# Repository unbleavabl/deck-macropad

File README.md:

# Handwired macropad (tilted deck)

12 MX keys, 2 EC11 encoders, 3 slide pots and 5 small OLED screens on a 30 degree wedge with a phone slot across the back. Handwired; an optional plate PCB that replaces the plate wiring is in `pcb/`. Runs on an STM32F411 "BlackPill" with QMK, USB-C only, no battery.

Everything lives in [`macropad/`](macropad/); file paths below are relative to it.

```
 +---------------------------------------------+
 | ========== phone slot (recessed) ========== |   back, 100 mm tall
 |                                             |
 |  ||   ||   ||   [K1]  [K2]  [K3]           |
 |  ||   ||   ||   [K4]  [K5]  [K6]    (E2)   |
 |  ||   ||   ||   [K7]  [K8]  [K9]    [S5]   |
 |  ||   ||   ||   [K10] [K11] [K12]   (E1)   |
 | [S1] [S2] [S3]                      [S4]   |   front, 13 mm tall
 +---------------------------------------------+
                  177 x 150 mm
```

Keys on a 21 mm grid (about 3 mm between caps), centred between the slider screens and the knob column, 5 mm margins each side; E2 is level with the top key row and E1 sits just behind S4. Each screen sits in front of its slider or knob. Every outside edge is rounded (2.5 mm, vertical corners 6 mm).

```
```

Beginner step-by-step guide with illustrations: `build-guide.pdf` (exported from the live doc at https://claude.ai/code/artifact/070e5841-1c04-4409-ae30-39a42349cde0; re-export after editing it).

Plate PCB (optional, replaces step 4 of the assembly and the plate end of the wiring; lid unchanged): `pcb/README.md`.

Full wiring diagram: `wiring/wiring.html` (regenerate with `wiring/build.py`), published at https://claude.ai/artifact/4pcYRyfMjdKxRtB2dDA4gZ. One drawing, to scale, shows the case opened up for wiring: lid (BlackPill, multiplexer, buttons) on top, turned round, plate underside below, their back edges at the fold. Bare copper buses are thick lines, insulated wires thin. The 27 wires between plate and lid are soldered at the plate end, gather along its back edge into five flat ribbons, and end in five multi-pin Dupont plugs on header pins, so the lid unplugs; each wire's number is on its line and in the harness table. Click a part, bus or number to see only its wires.

Firmware: QMK for the BlackPill in `firmware/deck` (keymaps `default` and `test`, layout and daemon below). The pin map below is final. Screens: Quantum Painter's `sh1106_i2c` driver (it covers the SSD1306), 128x64 at 0x3C, on I2C1 (B6 / B7, 400 kHz); before drawing to a screen, write `1 << channel` to the TCA9548A at 0x70.

## Parts

| Part | Qty | Notes |
|---|---|---|
| STM32F411CEU6 "BlackPill" (WeAct or clone) | 1 | chip must read STM32F411CEU6, crystal 25.000 |
| MX switches | 12 | |
| EC11 encoder, 5 pin (with push) | 2 | have |
| Bourns PTA4543-2015DPB103 slide pot (45 mm, 10k linear) | 3 | caps printed: `case/stl/knobs-caps/fader_cap.stl` |
| 0.96" OLED 128x64 SSD1306, 4-pin I2C | 5 | have; SDA SCL GND VCC from the back, all at address 0x3C |
| TCA9548A I2C multiplexer breakout | 1 | one channel per screen, since they all share one address; hot-glued in the lid |
| 1N4148 diode, through-hole | 14 | 12 keys + 2 encoder pushes |
| 100 nF ceramic capacitor | 3 | one per slider, beside its body: pin 2 to the GND back bus |
| 6x6 mm tactile switch, 5 mm tall | 2 | have; B (BOOT0) and R (reset) in the lid |
| Solid-core wire 24-26 AWG | 2 colours | rows / columns |
| Silicone wire 28-30 AWG | several colours | jumpers on the plate; use the wiring page's colours |
| Rainbow ribbon cable, 1.27 mm pitch | ~1 m | the 27 plate-to-lid wires, as five ribbons |
| Male header strip, 2.54 mm | 2 x 20 + mux | soldered on the BlackPill and multiplexer, long pins up |
| Dupont housings + female crimps | 1x10 x2, 1x5, 1x3, 1x1 | plugs A-E (below); or F-F jumpers cut and soldered |
| M3 x 8 flat-head (countersunk) screw | 10 | 4 plate (2 into the frame, 2 into the dock), 2 dock strip, 4 lid; they cut their own thread in the printed holes, no inserts. M3 x 10 grips better |
| Hot glue | | slide pots and screens sit on printed pegs under the plate; BlackPill and buttons in the lid |
| Rubber feet | 4 | |
| Keycaps 1u | 12 | printed: `case/stl/keycaps/` (flat, black, pressed-in labels) |
| ST-Link V2 (optional) | 1 | rescue flashing over SWD if USB DFU fails |

## Matrix and pins

4 rows x 4 columns, `col2row`: diode anode on the switch, **black band toward the row wire**. Column 3 holds only the two encoder pushes, each on the row nearest it; the push pin nearer the keys takes the diode.

```
          col0 (A7)   col1 (A8)   col2 (A15)  col3 (B0)
row0 A4     K1          K2          K3          E2 push
row1 A5     K4          K5          K6          -
row2 A6     K7          K8          K9          E1 push
row3 B14    K10         K11         K12         -
```

| Signal | BlackPill pin |
|---|---|
| Encoder 1 A / B | B1 / B8 |
| Encoder 2 A / B | B9 / A0 |
| Encoder C (middle of the 3 pins, both) | G |
| Slide pot pin 2 (wiper), sliders 1 / 2 / 3 | A1 / A2 / A3 (ADC1_IN1-3) |
| Slide pot pin 1 (all three) | 3V3 |
| Slide pot pin 3 (all three, alone at the front end) | G, by a short jumper to its own screen's GND pin; 100 nF beside the slider (right of it, from the back), pin 2 to the GND back bus |
| Screens GND / VCC (all five) | G / 3V3 |
| Multiplexer SCL / SDA (I2C1) | B6 / B7 |
| Multiplexer VIN / GND | 3V3 / G |
| Screen SDA / SCL, S1 S2 S3 S4 (E1) S5 (E2) | mux channels 0 1 2 3 4 (SDn / SCn) |
| R button | R (NRST) and G |
| B button | across the board's own BOOT0 button (BOOT0 has no pin hole) |

Avoid: A9 (USB VBUS sense, internal pull-down), A10 (can stop DFU), A11 / A12 (USB), B2 (BOOT1), C13 (LED), C14 / C15 (32 kHz crystal). B14 is row 3. Free: B3, B4, B5, B10, B12, B13, B15. A0 shares the board's KEY button, which is fine for an encoder input. A4-A7 also go to the optional SPI flash footprint on the back: fine as long as no flash chip is fitted. Pin caveats from the [QMK BlackPill notes](https://docs.qmk.fm/platformdev_blackpill_f4x1).

**Plugs on the header pins** (mark pin 1 of each plug and its header):

| Plug | Pins | Wires |
|---|---|---|
| A, 1x10 | BlackPill A0 A1 A2 A3 A4 A5 A6 A7 B0 B1 | 14 15 16 17 1 2 3 5 8 11 |
| B, 1x10 | mux SD0 SC0 SD1 SC1 ... SD4 SC4 | 18-27 |
| C, 1x5 | B8 B9 (5V empty) G 3V3 | 12 13 9 10 |
| D, 1x3 | B14 (B15 empty) A8 | 4 6 |
| E, 1x1 | A15 | 7 |

The lid's own wires: mux SCL / SDA to B6 / B7, mux GND / VIN to G / 3V3 on the other header, and the two buttons.

**Wiring happens upside down, so everything is mirrored.** From below, K1 is at the top right, the sliders are on the right and the knob column is at the left.

## Flashing

- USB DFU: hold B, tap R, let go of B; the board shows up as `STM Device in DFU Mode` (`lsusb`). Flash with `dfu-util` / `qmk flash`. If it won't enter DFU, retry, or add a 22k pull-up on A10.
- A `QK_BOOT` key in the keymap covers day-to-day flashing.
- Rescue: ST-Link V2 on the 4-pin SWD header (3V3 sense, DIO = PA13, SCK = PA14, G), board powered over USB. `st-info --probe` should report chip id `0x431`; `st-flash write firmware.bin 0x08000000`.

## Case (case/)

Rebuild every STL and preview with `case/build.sh` (OpenSCAD 2021.01).

```
case/
  build.sh        all STLs + previews
  diagram.py      preview/assembly.png (run by build.sh)
  scad/
    common.scad   shared sizes: key grid, switch/encoder holes, screws, screen module, lid
    deck.scad     the deck: plate, phone dock, frame, lid
    parts.scad    encoder knobs and spacers, slider caps, fit tests
    keycaps.scad  flat keycaps and their pressed-in labels
    fonts/        DeckIcons.ttf: Material Symbols Rounded, filled, weight 600, for the label icons
    exploded.scad exploded view for the diagram (not a print)
  stl/
    fit-tests/    print these first
    deck/         plate, frame, lid
    knobs-caps/   knobs, encoder spacers, slider caps
    keycaps/      keycap, label set (body + legend), blank label
  3mf/            ready-to-print Bambu Studio projects for the keycaps (make_3mf.py)
  stickers/       the key icons as A4 sticker sheets, white paper and clear film (make_stickers.py);
                  text legends for DSA caps, yellow and black, 11 mm (make_text_stickers.py)
  preview/        renders; assembly.png shows which STL goes where
```

**What to print**

| STL | Qty | Notes |
|---|---|---|
| `fit-tests/fit_switch_encoder.stl` | 1 | One switch cutout and one encoder hole. **Print first.** Switches should click in firmly; the encoder bushing should pass through. Tune `switch_cut`, `enc_hole` in `common.scad` (`enc_hole` is 7.8: 7.3 printed too small for the thread). |
| `fit-tests/fit_screen.stl` | 1 | One screen pocket and window. Printed top face down; the arrow points at the header end. The module's glass should drop into the pocket, the lit area fill the window, the 4 pegs go through the mounting holes. Tune the `scr_*` sizes in `common.scad`; they are typical values, not measured. |
| `fit-tests/fit_knob_caps.stl` | 1 | 3 knobs with bores 6.30 / 6.34 / 6.38 mm (1-3 dots on top; 6.26 was tight, 6.46 very loose) and 4 slider caps with slots 4.0 x 1.0 to 4.3 x 1.3 mm (1-4 notches). Keep what grips, set `shaft_bore` / `lever_tol` in `parts.scad`. |
| `fit-tests/fit_knob.stl` | 1 | 3 short hubs (top 8 mm of the knob's bore) with bores 6.30 / 6.34 / 6.38 mm, 1-3 dots in the roof; quick to print. Keep the one that grips, set `shaft_bore` / `d_flat` in `parts.scad`. |
| `fit-tests/fit_keycap_caps.stl` | 1 | 3 keycaps with the MX cross at 4.0 x 1.2 / 4.1 x 1.3 / 4.2 x 1.4 mm (1-3 dots in the skirt's front edge). Black only, upright, no supports. Keep the one that pushes onto a switch firmly; set `cross` in `keycaps.scad`. |
| `fit-tests/fit_keycap_labels.stl` + `fit_keycap_legend.stl` | 1 | AMS test, one colour swap: load both as one object, black + white. 3 labels with 0.00 / 0.05 / 0.10 mm clearance each side (1-3 dots underneath), carrying the calculator (finest detail), region screenshot (thin strokes) and do-not-disturb (big white area) icons. Keep the one that presses into a test cap firmly and stays when the cap is shaken; set `label_tol`. |
| `fit-tests/fit_bp_cradle.stl` | 1 | 4 copies of the two ends of the lid's BlackPill cradle (front wall, rail ends; tied by thin bars), raised +0.4 / +0.8 / +1.2 / +1.6 mm (number on the base), each with a slice of the frame's back wall and its USB-C hole. Drop the board in upside down and plug a cable in: keep the one where the plug goes in straight and the board stays put, set `bp_raise` in `deck.scad` to its number, then rebuild and print `deck_lid`. |
| `deck/deck_plate.stl` | 1 | Sloped top in front of the phone slot, with all cutouts: 3 mm thick, 1.5 mm at every switch, encoder and pot, 0.8 mm over each screen, glue pegs underneath. 4 screws: 2 front corners into the frame, 2 back corners into the dock. Printed flat, top face down. |
| `deck/deck_dock.stl` | 1 | The phone dock: slot walls and floor, the strip of top behind the slot, and two screw blocks under the plate's back corners. Slides into notches in the frame's side walls; 2 screws through the strip into the frame. Printed standing on the slot floor, no supports. |
| `deck/deck_frame.stl` | 1 | Walls of the wedge, printed upright, notched in both side walls for the dock. USB-C in the back wall. |
| `deck/deck_lid.stl` | 1 | Flat bottom with the BlackPill cradle and pockets for the BOOT0 and reset buttons (marked B and R underneath). The BlackPill goes in upside down (chips, buttons and USB-C facing the lid, long header pins up), resting its pin stubs on two rails; set `bp_usb_h` and `bp_stub_h` in `deck.scad` from calipers. |
| `knobs-caps/knob.stl` | 2 | Encoder knob, 17 mm across, 17.5 mm tall: covers the uncut 20 mm shaft under a 0.8 mm roof, reaching 2 mm further down the shaft (`knob_skirt`). Plain D bore copied from a Stream Deck+ knob that fits these shafts (6.16 mm, 4.59 mm across the flat). Recess underneath clears the bushing. Upside down, no supports. |
| `knobs-caps/enc_spacer.stl` | 2 | 3 mm spacer ring on the encoder bushing under the plate, so the encoder and its shaft sit 3 mm lower. About 2.5 mm of thread is left above the plate: enough for the nut without its washer if your thread reaches; otherwise hot-glue the spacer to the plate and the encoder to the spacer. Thickness is `enc_spacer` in `common.scad`; the knob gets shorter to match (0 = no spacer). |
| `knobs-caps/fader_cap.stl` | 3 | Cap for the Bourns PTA slide-pot lever (4 x 1 mm metal blade). Upside down. |
| `keycaps/keycap.stl` | 12 | Flat blank MX cap, 18 x 18 x 6.8 mm, black. Printed upright (skirt and stem post on the bed), no supports: the only bridge is the cavity ceiling, at most ~5 mm from skirt to post. A 15.2 mm square pocket, 1.8 mm deep, in the top takes a pressed-in label flush with the top; an eject hole in the pocket floor beside the post. |
| `keycaps/label_body.stl` + `keycaps/label_legend.stl` | 1 set | The 12 labels (icons from `~/.config/deckd/config.toml`), face up, laid out as on the pad. Load both STLs as **one object with two parts** (Bambu Studio / Orca: import both, answer yes to "load as a single object with multiple parts"), body black, legend white. The black body is the bottom 1.0 mm and the white legend the top 0.8 mm (4 layers at 0.2) standing on it, so the AMS swaps colour once. No supports. The legend is flush with the cap top; the black around it sits 0.8 mm lower. |
| `keycaps/label_blank.stl` | spare | One plain black label, full height. Single colour: print it with the caps, not with the label set (it would add a swap every layer). |

**Settings**

- `common.scad`: `switch_cut`, `enc_hole`, `enc_spacer`, `enc_bush_l`, `clip_t`, screw sizes and `pilot_d` (the hole M3 screws thread into), glue peg size `peg_d`, screen module sizes (`scr_*`), `usb_cut`, `tol`.
- `deck.scad`: `tilt` (the Foxwood stand is 24.8), `front_h`, `block_b` (sliders along the slope), `key_block_b` (keys), `side_m` (side margins), edge rounding (`corner_r`, `edge_r`, `lip_r_front`, `lip_r_back`, `slot_chamfer`), `key_pitch` (21), `pot_pitch` (26, a screen module plus a gap), `scr_b` (front screen row), `enc_gap` (knob to the screen in front of it), dock screw blocks (`dock_ledge`, `dock_ledge_d`, `dock_pilot`), `pad_w` (plate width, fixed at 177.2), BlackPill size and `bp_usb_z`, pot sizes and `pot_peg_d`, phone slot (`phone_t`, `phone_angle`, `phone_b`, `phone_depth`).
- `keycaps.scad`: `cross` (MX socket), `label_tol` (label in its pocket), `cap`, `cap_h`, `label_t`, `legend_d`, `rim`, `icon_size`, and `legends`: one entry per key, an icon (a Material Symbols codepoint as `"\uXXXX"`; look names up at fonts.google.com/icons) or 2-4 characters of text. Rebuild with `case/build.sh`.
- `parts.scad`: `enc_shaft_l` (15 or 20, measure from the bushing base), `knob_gap`, `knob_roof`, `enc_shaft` (`"D"` or `"round"`), `shaft_bore`, `d_flat`, `knob_d`, `lever`, `lever_tol`, `fader`.

**Keycaps.** Flat, blank, black, with a pressed-in label. Caps and labels print as separate jobs, none with supports: caps black only, labels with one black-to-white swap. Put the caps on the switches, then press each label in, icon upright as you face the pad. The pocket is square, so the label goes in any way round; friction holds it. To change one, pull the cap and push a paperclip up through the eject hole beside the stem.

**Keycap print files (`case/3mf/`).** Bambu Studio projects for a P1S 0.4 with 0.20mm Standard, Textured PEI plate at 65 / 60 °C, and PLA Basic, filament 1 black and filament 2 white (map them to your AMS slots when sending). Each piece is its own object; each label is one object with a black body part and a white legend part. All four slice with no supports; the label files swap colour once.

| File | What | Swaps |
|---|---|---|
| `fit_keycap_caps.3mf` | 3 fit-test caps | 0 |
| `fit_keycap_labels.3mf` | 3 fit-test labels | 1 |
| `keycaps.3mf` | 12 caps | 0 |
| `labels.3mf` | 12 labels, laid out as on the pad | 1 |
| `labels_blank_white.3mf` | 12 plain labels, filament 2 (white), for the clear stickers | 0 |
| `glue_labels.3mf` | 12 glue-on labels for a bought flat cap (below) | 1 |

`case/make_3mf.py` builds them from the STLs (run by `build.sh`); printer and filament settings come from `case/bambu_p1s_settings.json`, a project config exported by Bambu Studio 2.8 (a single-nozzle printer needs the 2x2 `flush_volumes_matrix`).

**Glue-on labels (bought caps).** For flat MX caps like KeyCap v4 (flat 18.4 mm square top, square edges, corners ~r 1.5): `case/3mf/glue_labels.3mf`, 12 plates 17.8 mm square (0.3 mm of cap left round each), 1.2 mm black base with the white icon standing 0.8 mm on it, icons 13 mm, each with a 3 mm brim (trim it off). Ironing is on for every top surface, so both the black background (at 1.2 mm, before the swap) and the icon tops are ironed; one colour swap, ~33 min. Glue them on with a thin layer of CA gel or contact adhesive, icon upright as you face the pad. Sizes are `glue_*` in `keycaps.scad`; STLs in `case/stl/glue/`.

**Stickers.** `case/stickers/stickers.pdf`: 9 sets of the 12 icons for sticker paper, A4, white icon on a black 14.6 mm square (just under the 15.1 mm label face), laid out like the pad. Only the black is printed; the white is the paper, so any printer works on white sticker paper. The black runs 1 mm past each cut line (thin white hairline), so a slightly-off cut still leaves a black edge on the black cap. Print at 100% / actual size and check the 50 mm bar. Stick them on blank labels (`label_blank.stl`) for a single-colour print, or use them as spares. `case/make_stickers.py` reads the icons from `keycaps.scad`, so the sheet follows any change there.

**Clear sticker film.** `case/stickers/stickers_clear.pdf` (6 sets). Clear film has no white, so the icon is left unprinted and a **white** label shows through it: print `labels_blank_white.3mf` (one colour), stick a sticker on each label with the icon centred, trim it flush with the label's edge with a craft knife (the black runs 1.5 mm past the 15.1 mm label face, no cut line), then press the label into its black cap. Laser prints are the most opaque on film; on inkjet use the transparency/film paper setting and let it dry.

**Phone slot.** The phone (sized for an iPhone 16 Plus in a case, `phone_t` = 11) sinks 15 mm in and leans back at 70 degrees; the slot floor is square to its walls. The slot is open at both side walls, so a phone wider than the deck fits in landscape and can charge from the side; in portrait the charging port is below the slot floor.

**Screens.** Each sits under the plate with its glass in a pocket, seen through a bevelled window in the 0.8 mm skin left above it, header toward the back. The window stops `scr_win_inset` (1 mm) inside the lit area, leaving a border. Four printed pegs go through the module's mounting holes; a dab of hot glue on each peg tip holds it. Keep glue off the glass. The slide pots are held the same way: 2 pegs into the threaded holes in each body's ends, glued. S4 and S5 sit in the encoder column, each in front of its knob.

## Assembly order

1. Print the fit tests; adjust and rebuild until they fit.
2. Run an M3 screw into each of the 8 posts of the frame and the 2 holes in the dock's screw blocks once and back it out, to cut the thread.
3. Plate, upside down on the table: clip in the switches; encoders with the spacer ring, nut on top (no washer) or hot glue, anti-rotation tab snipped; sliders and screens on their pegs, glued.
4. Wire the plate (`wiring/wiring.html`): lay the copper buses (sleeve every row/column crossing), then diodes, column joints, knob, slider and screen jumpers to the buses.
5. Lid: solder L5's two wires onto the BlackPill's own BOOT0 button first (it ends up underneath). BlackPill upside down in its cradle (chip side down, long pins up, USB-C at the back), multiplexer long pins up, glued right of the BlackPill seen from above (beside B6 / B7); glue them in, wire L1-L6 (mux to BlackPill, buttons). Then the 27 numbered wires: solder each at its plate end, run it along the plate's back edge to its ribbon, and crimp the five ribbons into plugs A-E. Leave ~3 cm of slack at the fold so the case opens like a book; sleeve or lace the ribbons there.
6. Test with a meter, USB unplugged (the checklist at the end of `wiring.html`).
7. Close: slide the dock into the frame and screw its strip down (2 M3 x 8), then the plate (4 M3 x 8: 2 front into the frame, 2 back into the dock), lid from below (4 M3 x 8). Turn each screw backwards until it clicks into its thread before tightening.

## Keys, knobs, sliders (host/)

The `default` keymap only reports: every key, knob push, knob click and slider move goes to `host/deckd.py`, a background daemon (no UI), which runs what `~/.config/deckd/config.toml` says and draws all five screens. Change a key by editing that file and `systemctl --user restart deckd`; no reflashing.

- Keys: one shell command each (`run = "..."`), mostly Omarchy's own scripts.
- E1: seek 5 s a click, hold the push and turn for previous / next track, push alone = play / pause (S4: track title and elapsed time). E2: night light temperature, push = on/off (S5).
- Sliders: S1 output volume, S2 volume of the focused window's app (S2 shows its name), S3 brightness of all monitors over DDC/CI (`ddcutil`, ~0.3 s per change). A slider acts only when moved, not when the pad connects.
- Browsers: Chromium plays every tab through one audio stream, so S2 can't tell browser windows apart from outside. `host/browser/` has a small extension that fixes that: with a browser window focused, S2 sets the volume of the media in that window's active tab (YouTube through its own player, so its slider follows) and S2's screen shows the site. Set up once: `host/browser/install.sh` (registers the native messaging host for Chromium and Chrome), then chrome://extensions, Developer mode, Load unpacked, `host/browser/extension`.
- Without the daemon the keys do nothing and S1-S3 show the raw slider positions.

```bash
host/install.sh                     # systemd user service, config to ~/.config/deckd/config.toml
journalctl --user -u deckd -f       # log, shows each command it runs
systemctl --user restart deckd      # after editing the config
host/draw_layout.py                 # redraw host/layout.png from the config
host/deckd.py boot                  # bootloader, then: qmk flash -kb handwired/deck -km default
```

`firmware/flash.sh [keymap]` does both steps (build, jump, flash) with no hands on the pad. Bootloader without the daemon: hold both knob pushes for three seconds (`deck.c`). Needs `python-hidapi`, `pactl`, `hyprctl`, `ddcutil`.

`helper/` is the older joystick-axis slider helper, superseded by `host/`.

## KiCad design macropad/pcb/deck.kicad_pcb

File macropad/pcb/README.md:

# Plate PCB (v1, not yet ordered)

One 2-layer board under the plate that replaces the plate's handwiring: rows, columns, diodes, power buses and screen jumpers. Fits the printed parts as they are: no plate, frame, dock or lid reprint. Same pins as the handwired build, so the firmware doesn't change.

## How it sits

- Parallel to the plate, its top face 5 mm below the plate's top, the standard MX height. The switches clip into the plate and solder to the board. The board hangs from their pins and the screens' pins; it has no screws.
- **Screens** sit on their glue pegs as before, 0.4 mm above the board. Their 4 header pins go straight through it. Pry the black plastic spacer off each module's pins first (flush cutters under it, lever it down the pins). Pin order on the board, left to right seen from the top: **GND VCC SCL SDA**. Check it against your module's printing before soldering. The pegs pass through 3.2 mm holes.
- A **window under each screen** (17 x 21 mm) clears the parts on the module's back. Check that none of those parts sits outside the window, i.e. within ~2.5 mm of the header row.
- **Slide pots and encoders** are too tall to solder flat (the pots are about 7 mm deep, the encoders 6.5 mm plus the 3 mm spacer). They keep their plate mounts and pass through cutouts. A short wire joins each pin to a labelled pad beside its cutout:
  - pot: pins 1 and 2 at the back end, pads `1` (3V3) and `2` (wiper); pin 3 at the front end, pad `3` (GND). The 100 nF cap is on the board (C1-C3).
  - encoder: column of 5 pads left of the cutout, front to back `A C B SW SW` (A, C, B = the 3-pin side; the two SW pads take the two push pins, either way round). The push diode is on the board (D13, D14).
- **Lid unchanged.** The mux and BlackPill stay where they are, and plugs A-E stay as they are. The 27 ribbon wires solder into the pad groups A-E in the two channels between the key columns, one wire per labelled pad (silk names the BlackPill pin or mux channel). The square pad is each group's first pin. Empty positions (B15 in D, 5V in C) keep the plug spacing, so you can fit male headers and Dupont plugs at this end too.

## Parts on the board

| Ref | Part | Side |
|---|---|---|
| K1-K12 | MX switch (3- or 5-pin) | top, through the plate |
| D1-D14 | 1N4148, through-hole | bottom; band (square pad, `K`) toward the row |
| C1-C3 | 100 nF ceramic, 2.5 mm pitch | bottom |
| S1-S5 | the screens' own pins | top |
| JA-JE | harness wires (or 2.54 male headers) | from the bottom |
| J_P*, J_E* | pot / encoder lead pads | wires from the bottom |

## Build order

1. Solder diodes and caps on the bottom. Trim the leads flush on the top: there is only 2 mm under the plate.
2. Plate upside down: switches clipped in, screens on their pegs (spacers off the pins), pots and encoders mounted as before.
3. Lower the board onto the switch pins, screen pins and pegs together, then solder all of them.
4. Short wires from the pot and encoder pins to their pads.
5. Ribbon wires into JA-JE. Test with a meter, as in `wiring/wiring.html`'s checklist.

## Ordering (JLCPCB)

Upload `deck-gerbers.zip`. It's 169.3 x 105.1 mm, 2 layers, 1.6 mm, HASL, any colour. Over 100 mm, so the $2 price doesn't apply. Rules used: 0.25 mm tracks (a few necked to 0.15 at pads), 0.25 mm clearance, 0.35 mm via drill, GND pour on both layers.

**Before ordering**: print `fit-check-1to1.pdf` at 100 % (no "fit to page"), check a key's 14 mm square measures 14 mm, cut out the outline, and hold it under the plate. Every switch, peg, pot slot and encoder hole should line up.

## Rebuilding

`./route.sh` runs the whole thing: `build_pcb.py` places parts from the deck geometry (mirrors `case/scad/deck.scad`; change sizes there and here together), freerouting autoroutes, then GND pour, DRC (`drc.rpt`, must be clean), Gerbers, renders and the fit-check PDF. Needs KiCad 10 (`pacman -S kicad kicad-library`), Java 25 (`mise install java@temurin-25`) and `freerouting-2.5.0.jar` in `~/.cache/freerouting/` (GitHub releases). `deck.kicad_pcb` opens in KiCad for hand edits, but `route.sh` overwrites it.

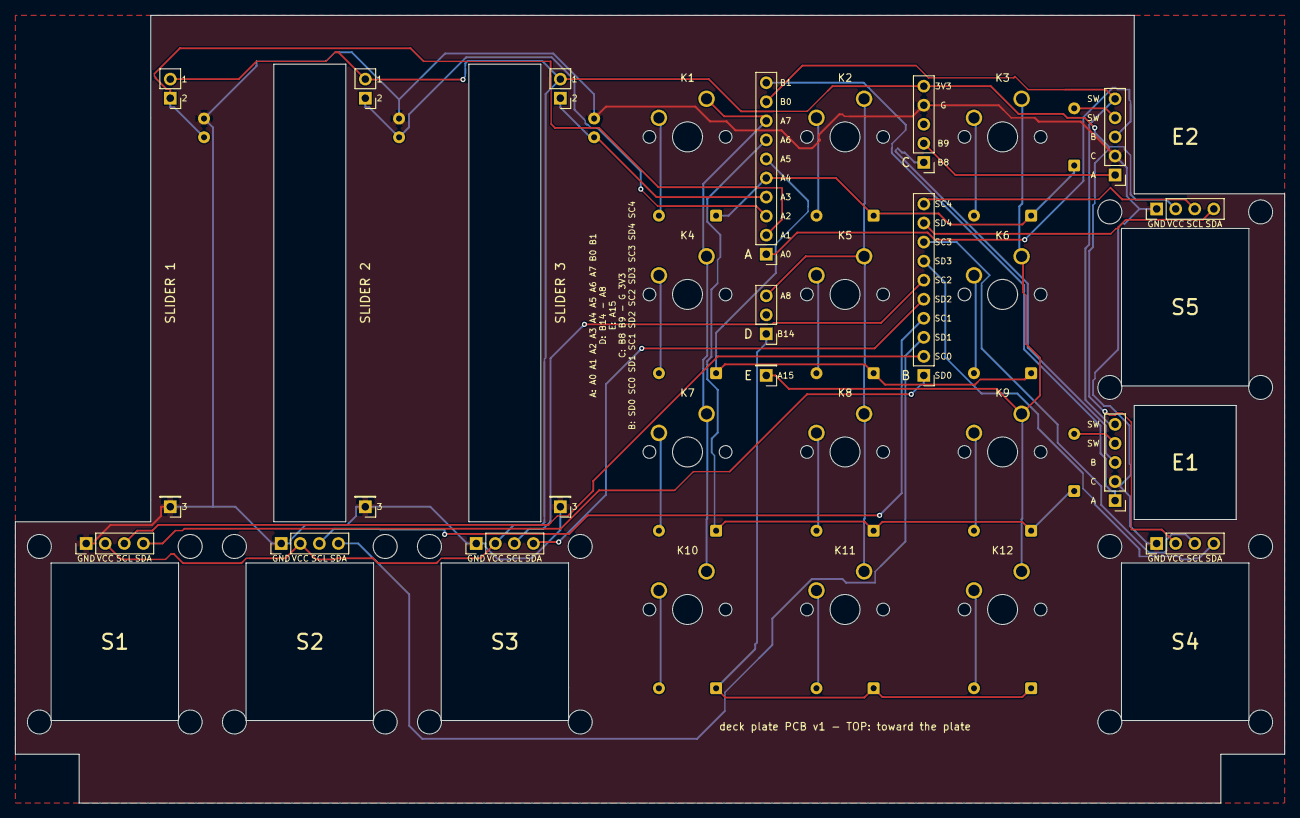
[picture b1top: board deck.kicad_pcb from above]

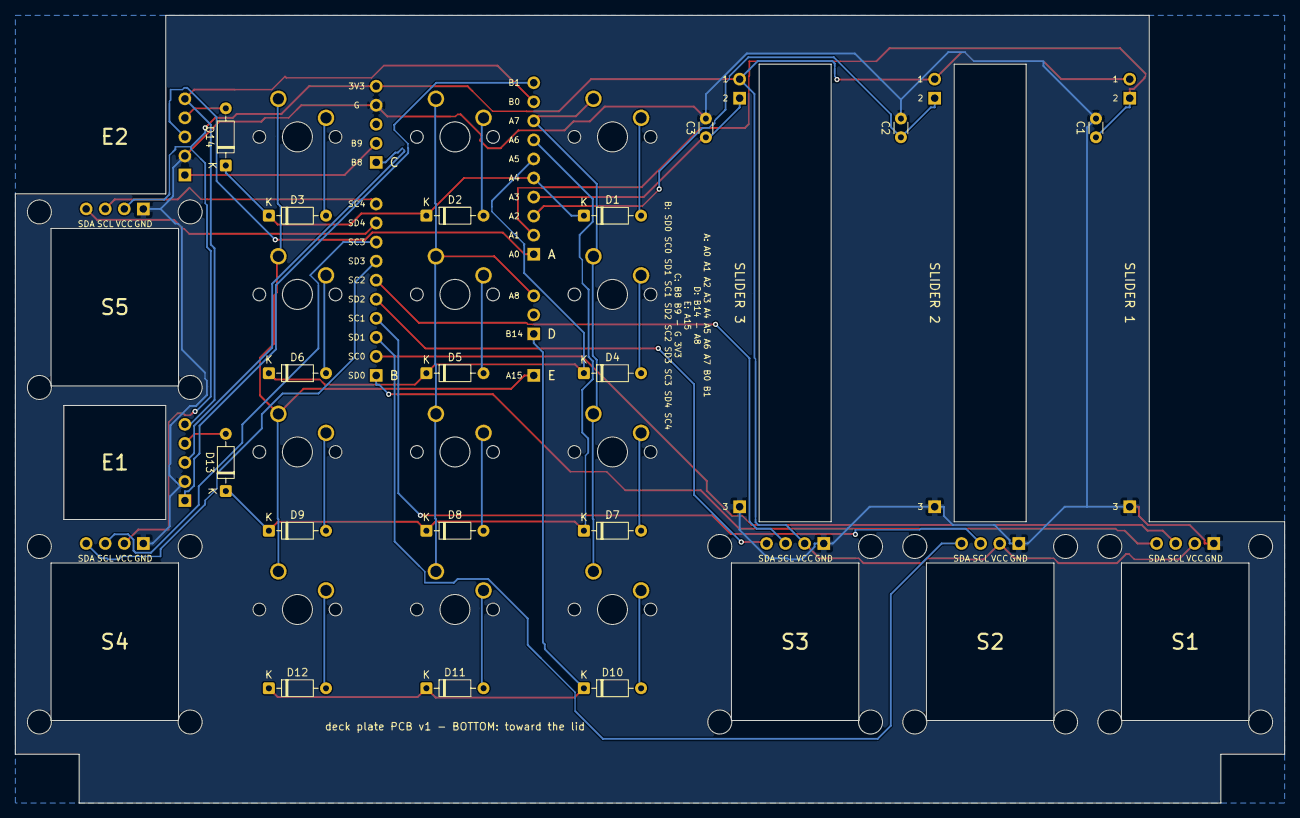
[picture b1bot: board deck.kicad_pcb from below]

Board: 2 copper layers, 169.2 x 105.0 mm, 67 parts (17 on the bottom side), 41 nets.

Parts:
C1, C2, C3: 100n; C_Disc_D3.0mm_W1.6mm_P2.50mm
D1, D2, D3, D4, D5, D6, D7, D8, D9, D10, D11, D12, D13, D14: 1N4148; D_DO-35_SOD27_P7.62mm_Horizontal
H1LB, H1LF, H1RB, H1RF, H2LB, H2LF, H2RB, H2RF, H3LB, H3LF, H3RB, H3RF, H4LB, H4LF, H4RB, H4RF, H5LB, H5LF, H5RB, H5RF: peg; PegHole_3.2mm
JA: PinHeader_1x10_P2.54mm_Vertical
JB: PinHeader_1x10_P2.54mm_Vertical
JC: PinHeader_1x05_P2.54mm_Vertical
JD: PinHeader_1x03_P2.54mm_Vertical
JE: PinHeader_1x01_P2.54mm_Vertical
J_E1, J_E2: PinHeader_1x05_P2.54mm_Vertical
J_P1, J_P2, J_P3: PinHeader_1x02_P2.54mm_Vertical
J_P1G, J_P2G, J_P3G: PinHeader_1x01_P2.54mm_Vertical
K1, K2, K3, K4, K5, K6, K7, K8, K9, K10, K11, K12: MX; SW_Cherry_MX_1.00u_PCB
S1, S2, S3, S4, S5: PinHeader_1x04_P2.54mm_Vertical

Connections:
3V3: JC.5, J_P1.2, J_P2.2, J_P3.2, S1.2, S2.2, S3.2, S4.2, S5.2
COL0: JA.8, K1.1, K4.1, K7.1, K10.1
COL1: JD.3, K2.1, K5.1, K8.1, K11.1
COL2: JE.1, K3.1, K6.1, K9.1, K12.1
COL3: JA.9, J_E1.5, J_E2.5
E1A: JA.10, J_E1.1
E1B: JC.1, J_E1.3
E1P: D13.2, J_E1.4
E2A: JC.2, J_E2.1
E2B: JA.1, J_E2.3
E2P: D14.2, J_E2.4
GND: C1.2, C2.2, C3.2, JC.4, J_E1.2, J_E2.2, J_P1G.1, J_P2G.1, J_P3G.1, S1.1, S2.1, S3.1, S4.1, S5.1
K1D: D1.2, K1.2
K2D: D2.2, K2.2
K3D: D3.2, K3.2
K4D: D4.2, K4.2
K5D: D5.2, K5.2
K6D: D6.2, K6.2
K7D: D7.2, K7.2
K8D: D8.2, K8.2
K9D: D9.2, K9.2
K10D: D10.2, K10.2
K11D: D11.2, K11.2
K12D: D12.2, K12.2
POT1: C1.1, JA.2, J_P1.1
POT2: C2.1, JA.3, J_P2.1
POT3: C3.1, JA.4, J_P3.1
ROW0: D1.1, D2.1, D3.1, D14.1, JA.5
ROW1: D4.1, D5.1, D6.1, JA.6
ROW2: D7.1, D8.1, D9.1, D13.1, JA.7
ROW3: D10.1, D11.1, D12.1, JD.1
SC0: JB.2, S1.3
SC1: JB.4, S2.3
SC2: JB.6, S3.3
SC3: JB.8, S4.3
SC4: JB.10, S5.3
SD0: JB.1, S1.4
SD1: JB.3, S2.4
SD2: JB.5, S3.4
SD3: JB.7, S4.4
SD4: JB.9, S5.4
